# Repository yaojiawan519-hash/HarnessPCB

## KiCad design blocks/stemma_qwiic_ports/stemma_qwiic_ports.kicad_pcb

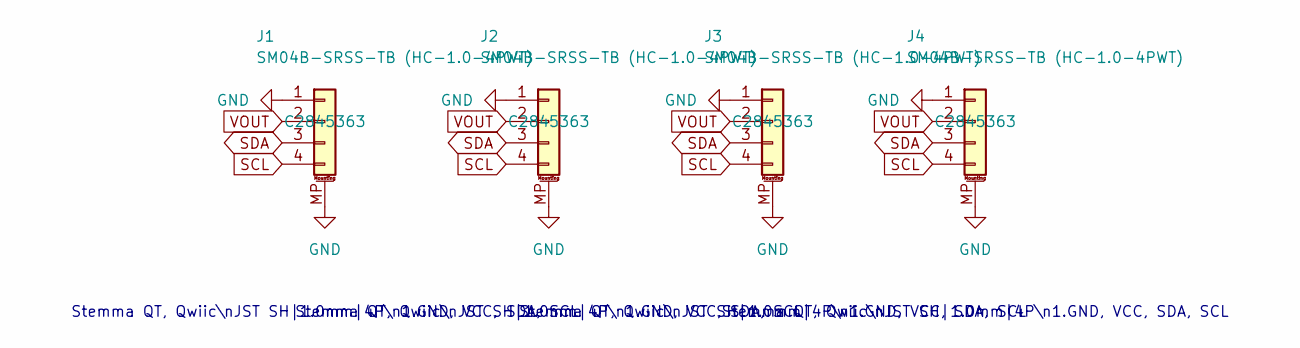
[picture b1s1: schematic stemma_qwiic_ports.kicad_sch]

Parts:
J1, J2, J3, J4: SM04B-SRSS-TB (HC-1.0-4PWT); JST_SH_SM04B-SRSS-TB_1x04-1MP_P1.00mm_Horizontal

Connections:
GND: J1.1, J1.MP (MountPin), J2.1, J2.MP (MountPin), J3.1, J3.MP (MountPin), J4.1, J4.MP (MountPin)
SCL: J1.4, J2.4, J3.4, J4.4
SDA: J1.3, J2.3, J3.3, J4.3
VOUT: J1.2, J2.2, J3.2, J4.2

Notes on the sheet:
Stemma QT, Qwiic\nJST SH|1.0mm|4P\n1.GND, VCC, SDA, SCL

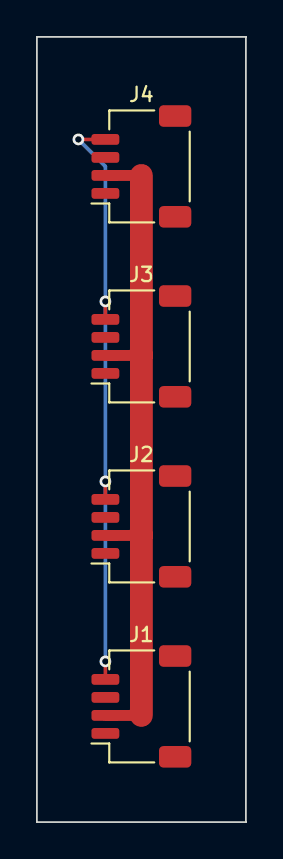
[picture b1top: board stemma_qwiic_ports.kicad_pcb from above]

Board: 2 copper layers, 11.6 x 43.6 mm, 4 parts (0 on the bottom side), 4 nets.

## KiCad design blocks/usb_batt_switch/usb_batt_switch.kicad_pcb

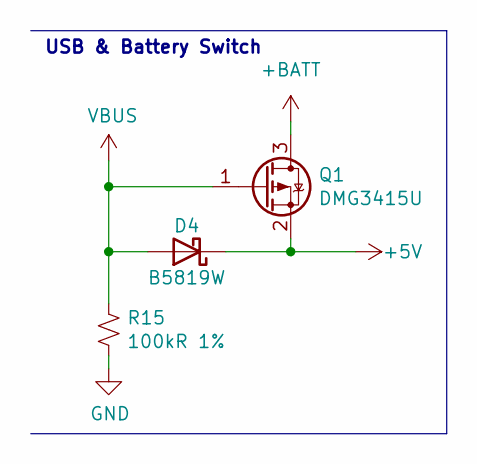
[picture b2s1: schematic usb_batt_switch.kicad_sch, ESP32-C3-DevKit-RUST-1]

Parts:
D4: B5819W; D_SOD-123; LCSC C8598
Q1: DMG3415U; SOT-23; LCSC C96616
R15: 100kR 1%; R_0402_1005Metric; LCSC C25741

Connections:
+5V: D4.1 (K), Q1.2 (S)
+BATT: Q1.3 (D)
GND: R15.2
VBUS: D4.2 (A), Q1.1 (G), R15.1

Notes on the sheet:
USB & Battery Switch

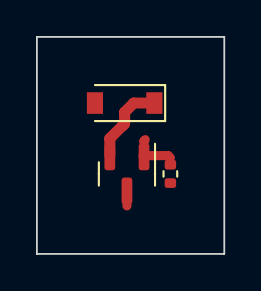
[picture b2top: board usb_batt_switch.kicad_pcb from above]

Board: 2 copper layers, 10.4 x 12.1 mm, 3 parts (0 on the bottom side), 2 nets.

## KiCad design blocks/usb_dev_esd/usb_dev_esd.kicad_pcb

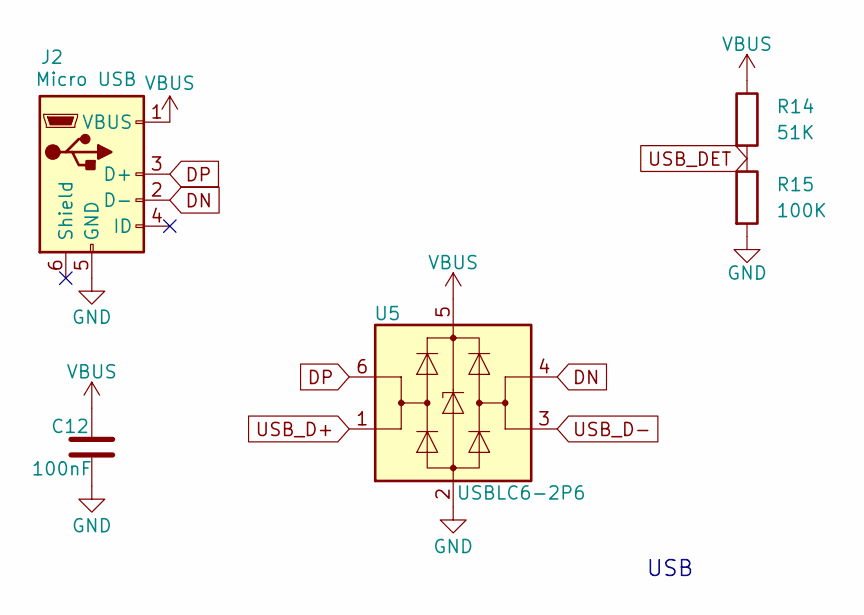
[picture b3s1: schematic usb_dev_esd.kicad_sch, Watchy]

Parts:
C12: 100nF; C_0402_1005Metric
J2: Micro USB; USB_Micro-B
R14: 51K; R_0402_1005Metric
R15: 100K; R_0402_1005Metric
U5: USBLC6-2P6; SOT-666

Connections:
DN: J2.2 (D-), U5.4 (I/O2)
DP: J2.3 (D+), U5.6 (I/O1)
GND: C12.2, J2.5 (GND), R15.2, U5.2 (GND)
USB_D+: U5.1 (I/O1)
USB_D-: U5.3 (I/O2)
USB_DET: R14.2, R15.1
VBUS: C12.1, J2.1 (VBUS), R14.1, U5.5 (VBUS)

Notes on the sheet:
USB

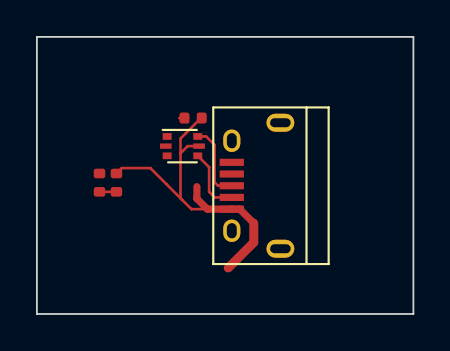
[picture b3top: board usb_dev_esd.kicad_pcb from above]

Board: 4 copper layers, 20.9 x 15.4 mm, 5 parts (0 on the bottom side), 5 nets.

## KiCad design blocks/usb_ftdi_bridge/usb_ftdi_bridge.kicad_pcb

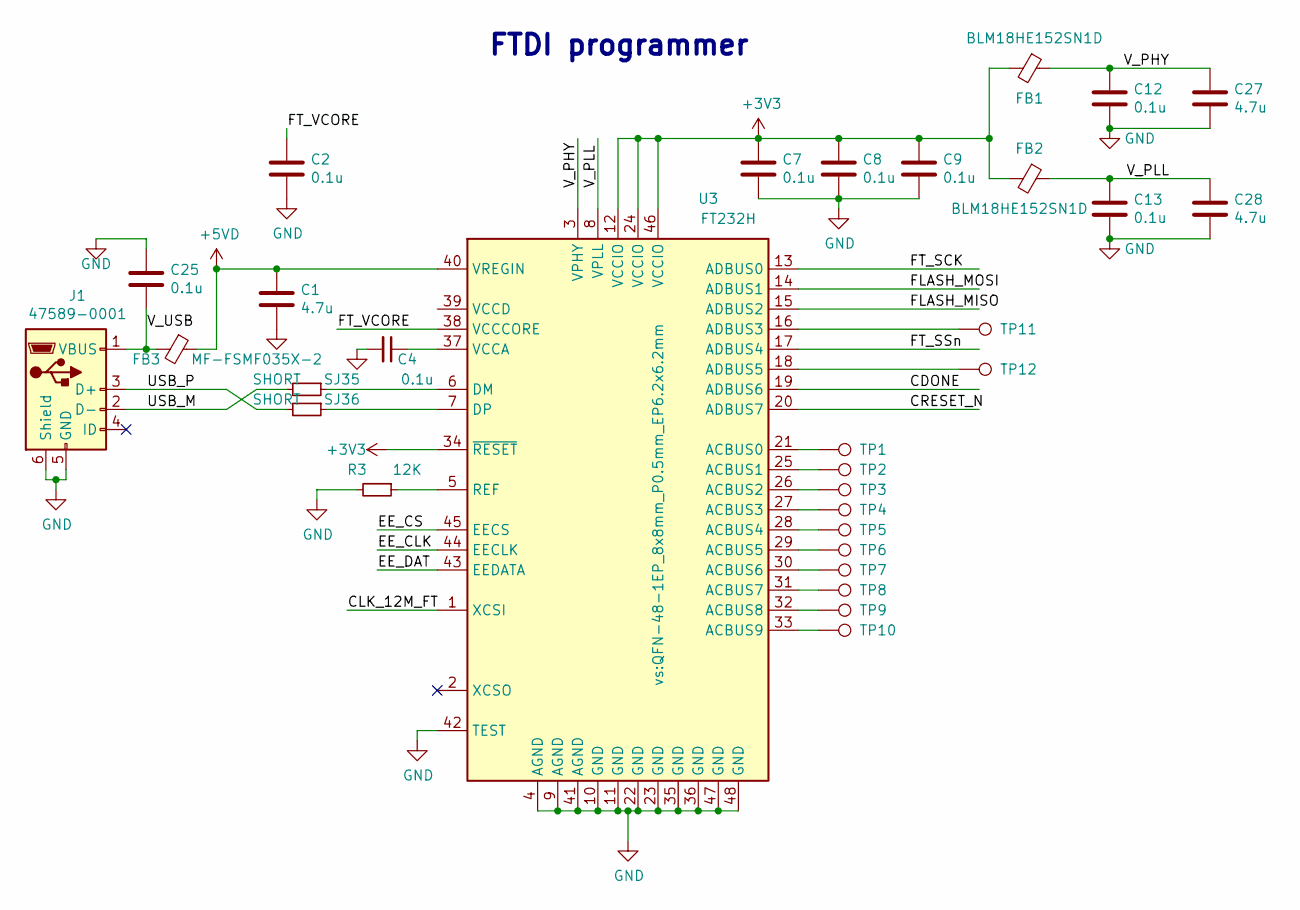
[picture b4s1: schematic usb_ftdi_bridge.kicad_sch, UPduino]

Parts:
C1, C27, C28: 4.7u; C_0603_1608Metric
C2, C4, C7, C8, C9, C12, C13, C25: 0.1u; C_0603_1608Metric
FB1, FB2: BLM18HE152SN1D; L_0603_1608Metric
FB3: MF-FSMF035X-2; L_0603_1608Metric
J1: 47589-0001; USB_Micro_AB_Female_0475890001
R3: 12K; R_0603_1608Metric
SJ35, SJ36: SHORT; ShortedJumper-2_P1.3mm_Bridged_Pad1.0x1.0mm
TP1, TP2, TP3, TP4, TP5, TP6, TP7, TP8, TP9, TP10, TP11, TP12: TestPoint; TestPoint_Pad_D1.0mm
U3: FT232H; QFN-48-1EP_8x8mm_P0.5mm_EP6.2x6.2mm

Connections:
+3V3: C7.1, C8.1, C9.1, FB1.2, FB2.2, U3.12 (VCCIO), U3.24 (VCCIO), U3.34 (~RESET), U3.46 (VCCIO)
+5VD: C1.1, FB3.1, U3.40 (VREGIN)
/CDONE: U3.19 (ADBUS6)
/CLK_12M_FT: U3.1 (XCSI)
/CRESET_N: U3.20 (ADBUS7)
/EE_CLK: U3.44 (EECLK)
/EE_CS: U3.45 (EECS)
/EE_DAT: U3.43 (EEDATA)
/FLASH_MISO: U3.15 (ADBUS2)
/FLASH_MOSI: U3.14 (ADBUS1)
/FT_SCK: U3.13 (ADBUS0)
/FT_SSn: U3.17 (ADBUS4)
/FT_VCORE: C2.1, U3.38 (VCCCORE)
/USB_M: J1.2 (D-), SJ35.2
/USB_P: J1.3 (D+), SJ36.2
/V_PHY: C12.1, C27.1, FB1.1, U3.3 (VPHY)
/V_PLL: C13.1, C28.1, FB2.1, U3.8 (VPLL)
/V_USB: C25.2, FB3.2, J1.1 (VBUS)
GND: C1.2, C2.2, C4.2, C7.2, C8.2, C9.2, C12.2, C13.2, C25.1, C27.2, C28.2, J1.5 (GND), J1.6 (Shield), R3.2, U3.4 (AGND), U3.9 (AGND), U3.10 (GND), U3.11 (GND), U3.22 (GND), U3.23 (GND), U3.35 (GND), U3.36 (GND), U3.41 (AGND), U3.42 (TEST), U3.47 (GND), U3.48 (GND), U3.49
unnamed: C4.1, U3.37 (VCCA)
unnamed: R3.1, U3.5 (REF)
unnamed: SJ35.1, U3.6 (DM)
unnamed: SJ36.1, U3.7 (DP)
unnamed: TP1.1, U3.21 (ACBUS0)
unnamed: TP2.1, U3.25 (ACBUS1)
unnamed: TP3.1, U3.26 (ACBUS2)
unnamed: TP4.1, U3.27 (ACBUS3)
unnamed: TP5.1, U3.28 (ACBUS4)
unnamed: TP6.1, U3.29 (ACBUS5)
unnamed: TP7.1, U3.30 (ACBUS6)
unnamed: TP8.1, U3.31 (ACBUS7)
unnamed: TP9.1, U3.32 (ACBUS8)
unnamed: TP10.1, U3.33 (ACBUS9)
unnamed: TP11.1, U3.16 (ADBUS3)
unnamed: TP12.1, U3.18 (ADBUS5)

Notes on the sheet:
FTDI programmer

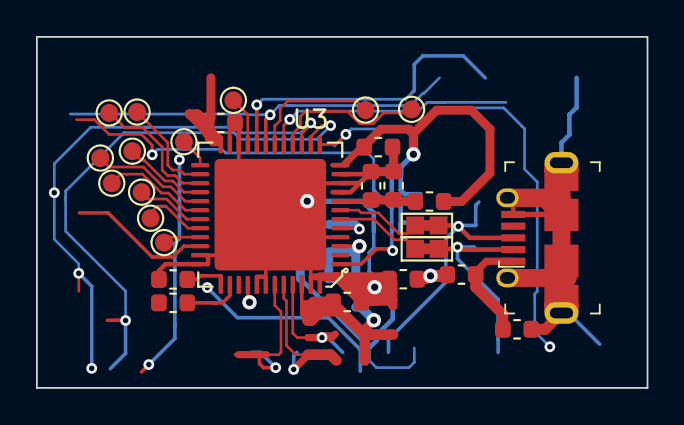
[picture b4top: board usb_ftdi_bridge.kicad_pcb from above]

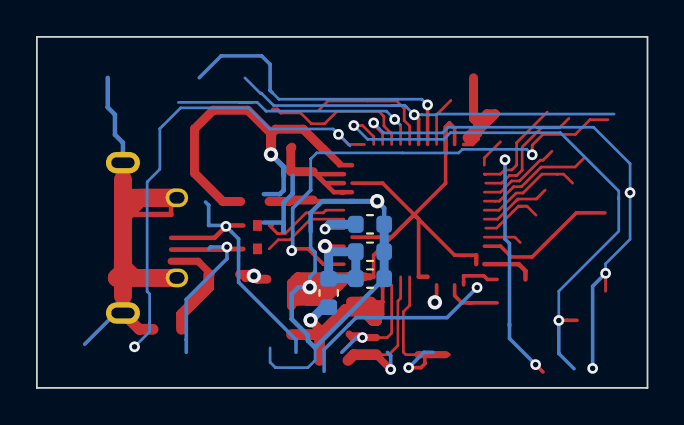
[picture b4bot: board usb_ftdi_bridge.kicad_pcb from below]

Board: 4 copper layers, 33.9 x 19.5 mm, 31 parts (4 on the bottom side), 25 nets.

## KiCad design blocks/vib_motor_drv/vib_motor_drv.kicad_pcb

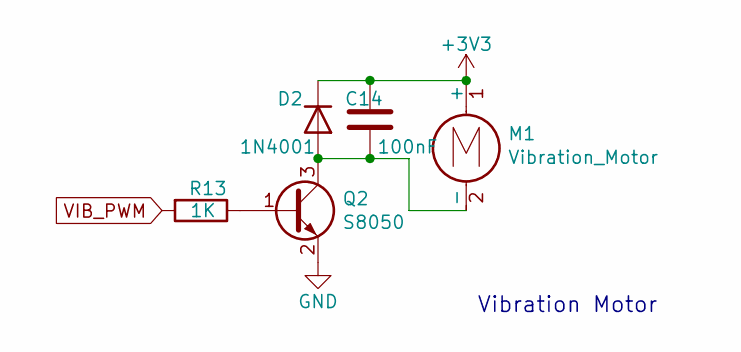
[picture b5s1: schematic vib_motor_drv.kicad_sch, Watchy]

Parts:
C14: 100nF; C_0402_1005Metric
D2: 1N4001; D_SOD-123F
M1: Vibration_Motor; Motor_Header
Q2: S8050; SOT-23
R13: 1K; R_0402_1005Metric

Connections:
+3V3: C14.1, D2.1 (K), M1.1 (+)
GND: Q2.2 (E)
unnamed: C14.2, D2.2 (A), M1.2 (-), Q2.3 (C)
unnamed: Q2.1 (B), R13.1
VIB_PWM: R13.2

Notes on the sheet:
Vibration Motor

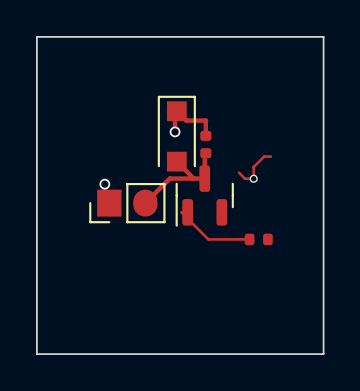
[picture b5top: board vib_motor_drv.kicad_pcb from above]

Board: 4 copper layers, 15.9 x 17.6 mm, 5 parts (0 on the bottom side), 3 nets.
